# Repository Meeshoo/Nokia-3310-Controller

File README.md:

# Nokia 3310 Controller
An AtmegaA32U4 powered PCB designed to replace the main board in a Nokia 3310, with Type C connector. Made in KiCad, running QMK firmware.

Custom footprints for the pads needs to be used.

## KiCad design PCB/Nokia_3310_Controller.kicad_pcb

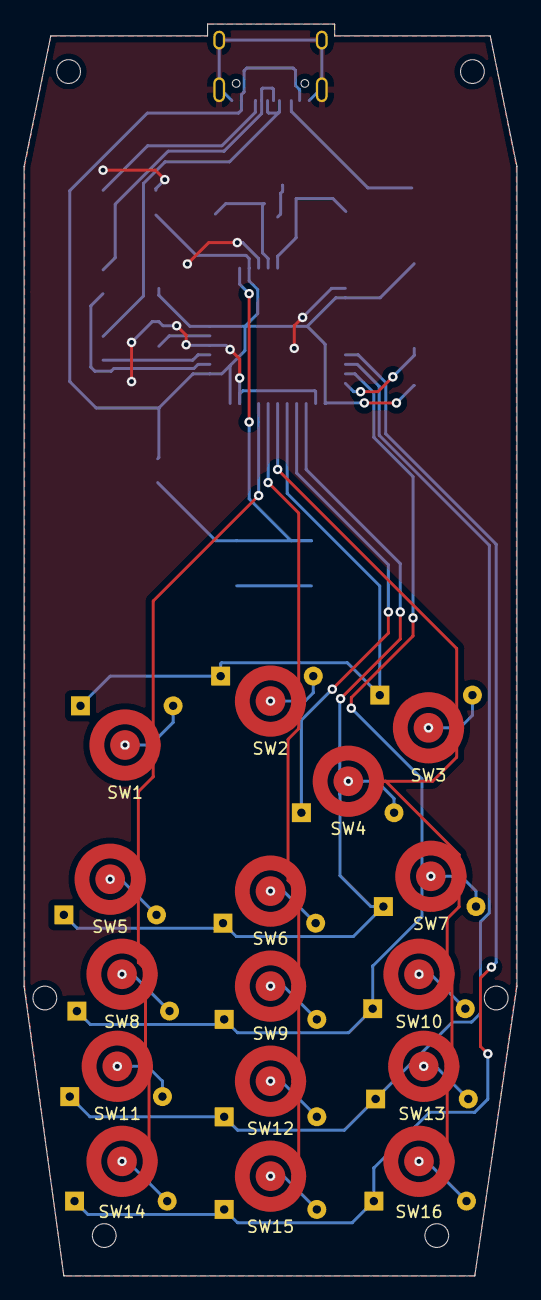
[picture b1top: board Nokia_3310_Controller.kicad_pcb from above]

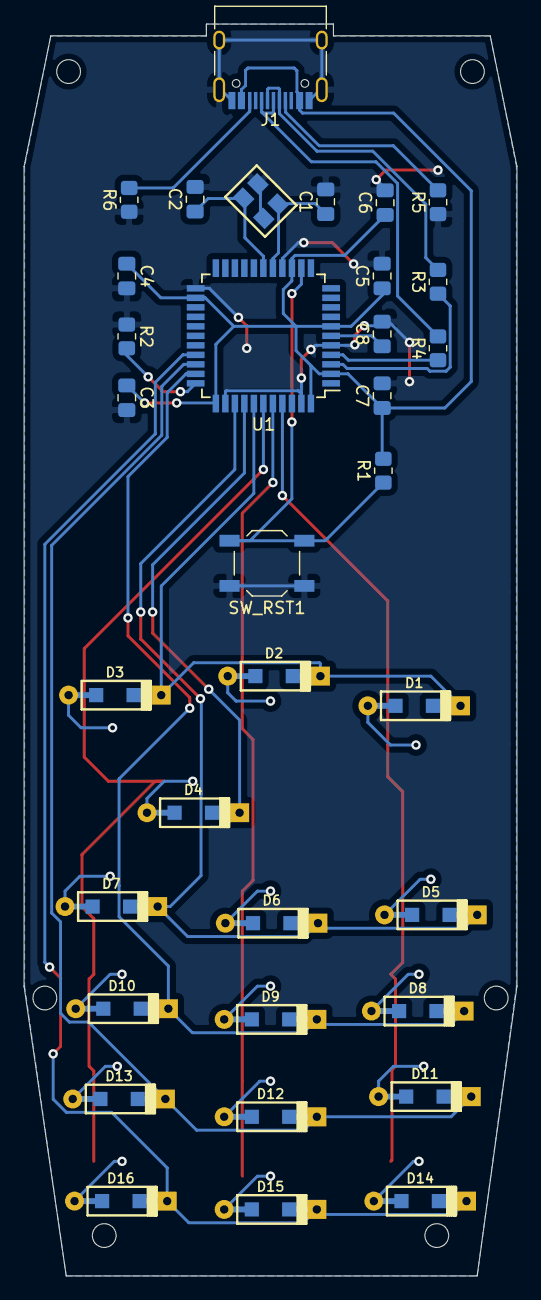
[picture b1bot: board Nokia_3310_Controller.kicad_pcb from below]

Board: 2 copper layers, 41.5 x 105.4 mm, 56 parts (34 on the bottom side), 38 nets.

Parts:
C1, C2: 22p; C_0805_2012Metric_Pad1.18x1.45mm_HandSolder
C3, C4, C5, C6: 0.1u; C_0805_2012Metric_Pad1.18x1.45mm_HandSolder
C7: 4.7u; C_0805_2012Metric_Pad1.18x1.45mm_HandSolder
C8: 1u; C_0805_2012Metric_Pad1.18x1.45mm_HandSolder
D1, D2, D3, D4, D5, D6, D7, D8, D9, D10, D11, D12, D13, D14, D15, D16: D; D_SOD123_axial
J1: USB_C_Receptacle_USB2.0; USB_C_Receptacle_HRO_TYPE-C-31-M-12
NPTH: Mount; Nokia_3310_MountHole
NPTH#2, NPTH#3, NPTH#5, NPTH#6: Mount; Nokia_3310_MountHole
NPTH#4: Mounr; Nokia_3310_MountHole
R1, R2: 10k; R_0805_2012Metric_Pad1.20x1.40mm_HandSolder
R3, R4: 22; R_0805_2012Metric_Pad1.20x1.40mm_HandSolder
R5, R6: 5.1k; R_0805_2012Metric_Pad1.20x1.40mm_HandSolder
SW1, SW2, SW3, SW4, SW5, SW6, SW7, SW8, SW9, SW10, SW11, SW12, SW13, SW14, SW15, SW16: SW_Push; Nokia_3310_ButtonPad
SW_RST1: SW_Push; SW_SPST_TL3342
U1: ATMEGA32U4; TQFP-44_10x10mm_P0.8mm
X1: XTAL_GND; FA-238

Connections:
/col0: SW1.1, SW5.1, SW8.1, SW11.1, SW14.1, U1.41
/col1: SW2.1, SW6.1, SW9.1, SW12.1, SW15.1, U1.40
/col2: SW3.1, SW4.1, SW7.1, SW10.1, SW13.1, SW16.1, U1.39
/row0: D1.1, D2.1, D3.1, U1.38
/row1: D4.1, U1.37
/row2: D5.1, D6.1, D7.1, U1.36
/row3: D8.1, D9.1, D10.1, U1.32
/row4: D11.1, D12.1, D13.1, U1.31
/row5: D14.1, D15.1, D16.1, U1.30
GND: C1.2, C2.2, C3.2, C4.2, C5.2, C6.2, C7.2, C8.2, J1.A1, J1.A12, J1.B1, J1.B12, J1.S1, R2.1, R5.1, R6.1, SW_RST1.1, U1.5, U1.15, U1.23, U1.35, U1.43, X1.3
unnamed: C1.1, U1.16, X1.1
unnamed: C2.1, U1.17, X1.2
unnamed: C8.1, U1.6
unnamed: D1.2, SW1.2
unnamed: D2.2, SW2.2
unnamed: D3.2, SW3.2
unnamed: D4.2, SW4.2
unnamed: D5.2, SW5.2
unnamed: D6.2, SW6.2
unnamed: D7.2, SW7.2
unnamed: D8.2, SW8.2
unnamed: D9.2, SW9.2
unnamed: D10.2, SW10.2
unnamed: D11.2, SW11.2
unnamed: D12.2, SW12.2
unnamed: D13.2, SW13.2
unnamed: D14.2, SW14.2
unnamed: D15.2, SW15.2
unnamed: D16.2, SW16.2
unnamed: J1.A5, R5.2
unnamed: J1.A6, J1.B6, R4.2
unnamed: J1.A7, J1.B7, R3.2
unnamed: J1.B5, R6.2
unnamed: R1.1, SW_RST1.2, U1.13
unnamed: R2.2, U1.33
unnamed: R3.1, U1.3
unnamed: R4.1, U1.4
VCC: C3.1, C4.1, C5.1, C6.1, C7.1, J1.A4, J1.A9, J1.B4, J1.B9, R1.2, U1.2, U1.7, U1.14, U1.24, U1.34, U1.44
